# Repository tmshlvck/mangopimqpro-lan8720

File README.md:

LAN8720 board for MangoPi MQ-Pro
================================

The schematic and PCB are in HW section. Feel free to make it, it is quite cool add-on board.
Schematic: [PDF](hw/meta/schematic.pdf)

I run it with the Nezha Ubuntu image with the patch applied using this:

* clone Linux kernel tree (`git clone https://github.com/torvalds/linux.git`)
* apply the patch from this repo (`git am 0001-Add-LAN8720a-PHY-to-MangoPI-MQ-Pro-board.patch`)
* build DTB `ARCH=riscv make dtbs`
* scp the result `arch/riscv/boot/dts/allwinner/sun20i-d1-mangopi-mq-pro-lan8720.dtb` to `/boot` on MangoPi MQ-Pro
* link the current kernel DTB to this file (in my case `cd boot; rm dtb-6.2.0-35-generic; ln -s sun20i-d1-mangopi-mq-pro-lan8720.dtb dtb-6.2.0-35-generic`)
* reboot the MangoPi MQ-Pro

License
-------

HW: The TAPR Open Hardware License Version 1.0
SW: GNU GPLv3

Expected dmesg output
---------------------

```
[  104.125393] dwmac-sun8i 4500000.ethernet: IRQ eth_wake_irq not found
[  104.125445] dwmac-sun8i 4500000.ethernet: IRQ eth_lpi not found
[  104.126653] dwmac-sun8i 4500000.ethernet: PTP uses main clock
[  104.126754] dwmac-sun8i 4500000.ethernet: Current syscon value is not the default 50006 (expect 0)
[  104.140716] dwmac-sun8i 4500000.ethernet: No HW DMA feature register supported
[  104.140764] dwmac-sun8i 4500000.ethernet: RX Checksum Offload Engine supported
[  104.140794] dwmac-sun8i 4500000.ethernet: COE Type 2
[  104.140826] dwmac-sun8i 4500000.ethernet: TX Checksum insertion supported
[  104.140857] dwmac-sun8i 4500000.ethernet: Normal descriptors
[  104.140885] dwmac-sun8i 4500000.ethernet: Chain mode enabled
[  108.505636] dwmac-sun8i 4500000.ethernet end0: renamed from eth0
[  111.253079] dwmac-sun8i 4500000.ethernet end0: PHY [stmmac-0:01] driver [SMSC LAN8710/LAN8720] (irq=POLL)
[  111.260378] dwmac-sun8i 4500000.ethernet end0: Register MEM_TYPE_PAGE_POOL RxQ-0
[  111.264987] dwmac-sun8i 4500000.ethernet end0: No Safety Features support found
[  111.265046] dwmac-sun8i 4500000.ethernet end0: No MAC Management Counters available
[  111.265085] dwmac-sun8i 4500000.ethernet end0: PTP not supported by HW
[  111.282125] dwmac-sun8i 4500000.ethernet end0: configuring for phy/rmii link mode
[  287.401778] dwmac-sun8i 4500000.ethernet end0: Link is Up - 100Mbps/Full - flow control rx/tx
```

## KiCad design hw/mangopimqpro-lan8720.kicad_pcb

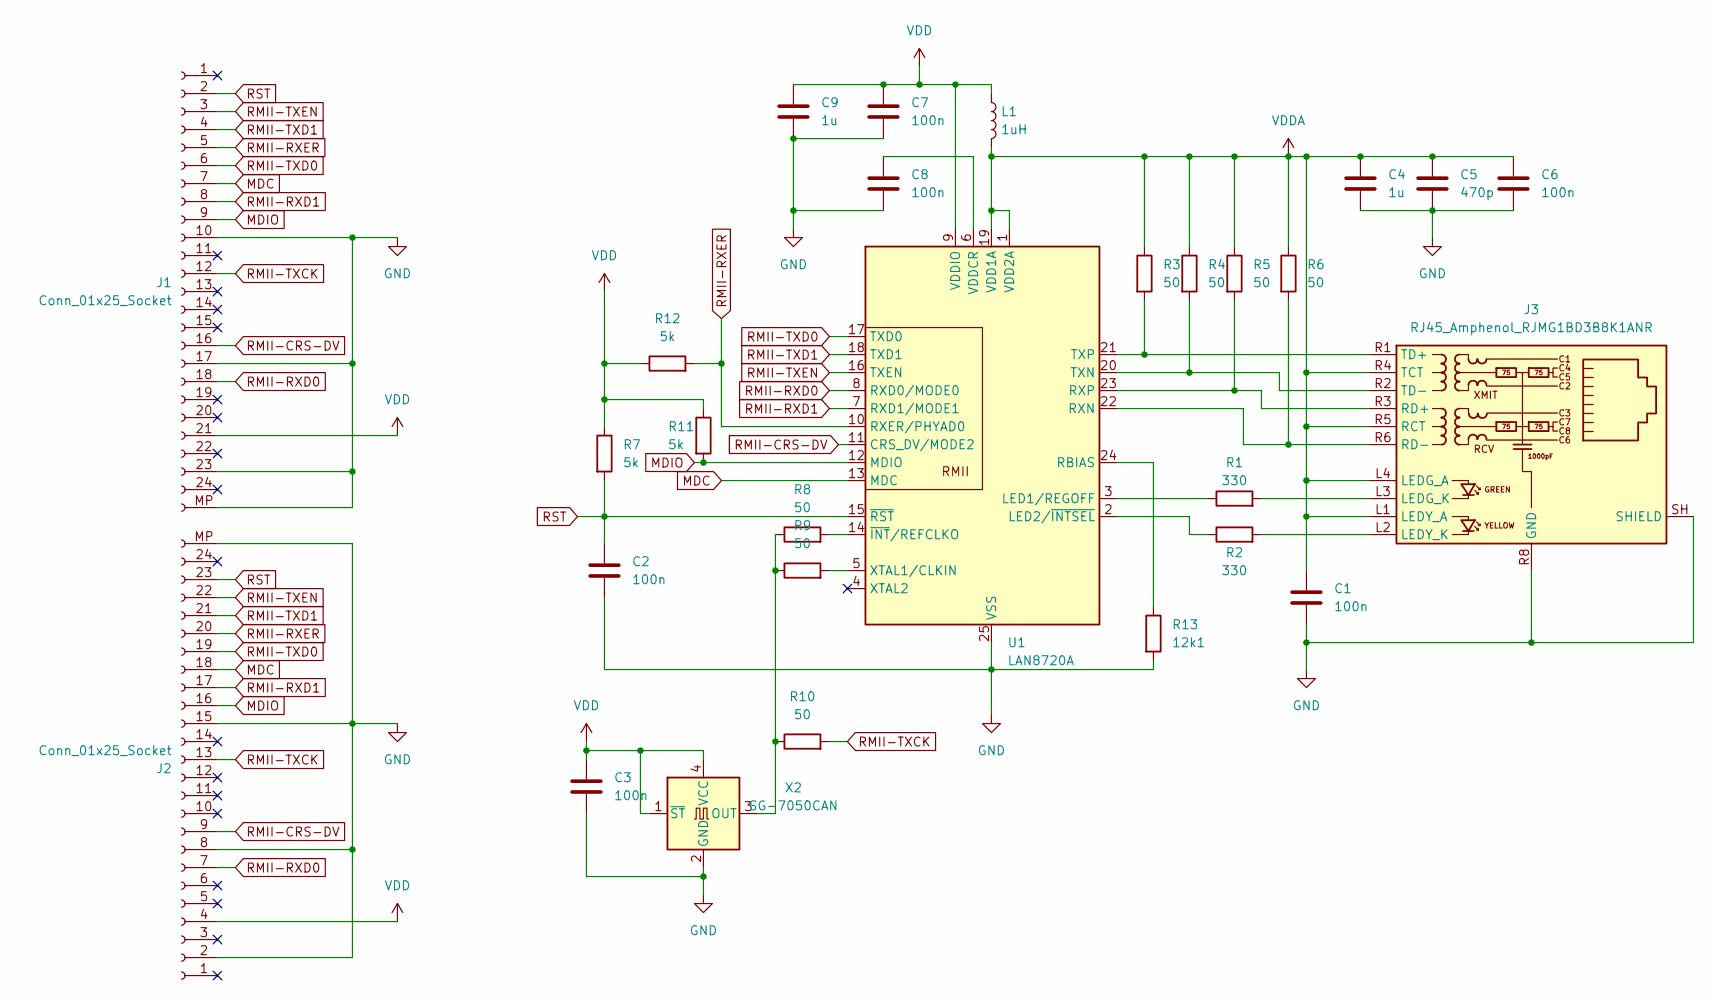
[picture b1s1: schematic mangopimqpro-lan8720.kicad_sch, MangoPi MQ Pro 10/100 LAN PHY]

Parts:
C1, C2, C3, C6, C7, C8: 100n; C_0805_2012Metric_Pad1.18x1.45mm_HandSolder
C4, C9: 1u; C_0805_2012Metric_Pad1.18x1.45mm_HandSolder
C5: 470p; C_0805_2012Metric_Pad1.18x1.45mm_HandSolder
J1, J2: Conn_01x25_Socket; Hirose_FH12-24S-0.5SH_1x24-1MP_P0.50mm_Horizontal
J3: RJ45_Amphenol_RJMG1BD3B8K1ANR
L1: 1uH; L_1206_3216Metric_Pad1.22x1.90mm_HandSolder
R1, R2: 330; R_0805_2012Metric_Pad1.20x1.40mm_HandSolder
R3, R4, R5, R6, R8, R9, R10: 50; R_0805_2012Metric_Pad1.20x1.40mm_HandSolder
R7, R11, R12: 5k; R_0805_2012Metric_Pad1.20x1.40mm_HandSolder
R13: 12k1; R_0805_2012Metric_Pad1.20x1.40mm_HandSolder
U1: LAN8720A; VQFN-24-1EP_4x4mm_P0.5mm_EP2.5x2.5mm_ThermalVias
X2: SG-7050CAN; Oscillator_SMD_SeikoEpson_SG8002CA-4Pin_7.0x5.0mm

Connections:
GND: C1.2, C2.2, C3.2, C4.2, C5.2, C6.2, C7.2, C8.2, C9.2, J1.10, J1.17, J1.23, J1.MP (Pin_25), J2.2, J2.8, J2.15, J2.MP (Pin_25), J3.R8 (GND), J3.SH (SHIELD), R13.2, U1.25 (VSS), X2.2 (GND)
MDC: J1.7, J2.18, U1.13 (MDC)
MDIO: J1.9, J2.16, R11.2, U1.12 (MDIO)
unnamed: J3.L3 (LEDG_K), R1.2
unnamed: J3.L2 (LEDY_K), R2.2
unnamed: J3.R3 (RD+), R5.2, U1.23 (RXP)
unnamed: J3.R6 (RD-), R6.2, U1.22 (RXN)
unnamed: J3.R1 (TD+), R3.2, U1.21 (TXP)
unnamed: J3.R2 (TD-), R4.2, U1.20 (TXN)
unnamed: R1.1, U1.3 (LED1/REGOFF)
unnamed: R2.1, U1.2 (LED2/~INTSEL)
unnamed: R13.1, U1.24 (RBIAS)
unnamed: C8.1, U1.6 (VDDCR)
unnamed: R9.2, U1.5 (XTAL1/CLKIN)
unnamed: R8.2, U1.14 (~INT/REFCLKO)
unnamed: R8.1, R9.1, R10.1, X2.3 (OUT)
RMII-CRS-DV: J1.16, J2.9, U1.11 (CRS_DV/MODE2)
RMII-RXD0: J1.18, J2.7, U1.8 (RXD0/MODE0)
RMII-RXD1: J1.8, J2.17, U1.7 (RXD1/MODE1)
RMII-RXER: J1.5, J2.20, R12.2, U1.10 (RXER/PHYAD0)
RMII-TXCK: J1.12, J2.13, R10.2
RMII-TXD0: J1.6, J2.19, U1.17 (TXD0)
RMII-TXD1: J1.4, J2.21, U1.18 (TXD1)
RMII-TXEN: J1.3, J2.22, U1.16 (TXEN)
RST: C2.1, J1.2, J2.23, R7.2, U1.15 (~RST)
VDD: C3.1, C7.1, C9.1, J1.21, J2.4, L1.1, R7.1, R11.1, R12.1, U1.9 (VDDIO), X2.1 (~ST), X2.4 (VCC)
VDDA: C1.1, C4.1, C5.1, C6.1, J3.L1 (LEDY_A), J3.L4 (LEDG_A), J3.R4 (TCT), J3.R5 (RCT), L1.2, R3.1, R4.1, R5.1, R6.1, U1.1 (VDD2A), U1.19 (VDD1A)

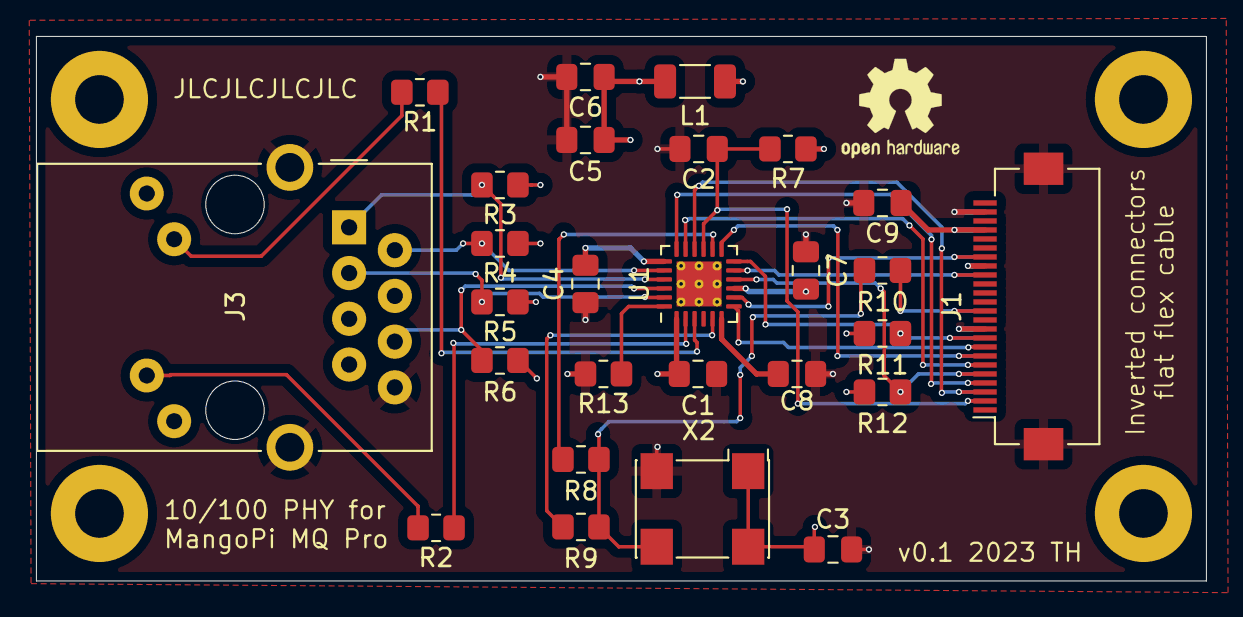
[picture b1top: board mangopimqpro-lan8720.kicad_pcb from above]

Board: 4 copper layers, 65.0 x 30.2 mm, 28 parts (1 on the bottom side), 27 nets.

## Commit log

2023-07-16 Inital commit
    Add basic README, pinout connections table and testing patch for Linux
    kernel to enable the breadboard experimental version of the future
    circuit.
2023-07-16 Add example dmesg output to README
    Capture example dmesg output to README from the breadboard experiment
2023-10-29 Add v0.1 board
    Add v0.1 board - schematic + PCB drawing + fabrication outputs
    Add new patch for MangoPi MQ-Pro
    Add patch application guide to README
    Add licenses for the artifacts
2023-10-29 Add board picture and links to README
2025-03-25 Fix typo in 0001-Add-LAN8720a-PHY-to-MangoPI-MQ-Pro-board.patch
    Fix typo in Makefile modification in 0001-Add-LAN8720a-PHY-to-MangoPI-MQ-Pro-board.patch
